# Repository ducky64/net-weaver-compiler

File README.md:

# net-weaver-compiler
Backend compiler for NetWeaver / WebEDG

See the live site at [https://leomcelroy.com/net-weaver/](https://leomcelroy.com/net-weaver/).

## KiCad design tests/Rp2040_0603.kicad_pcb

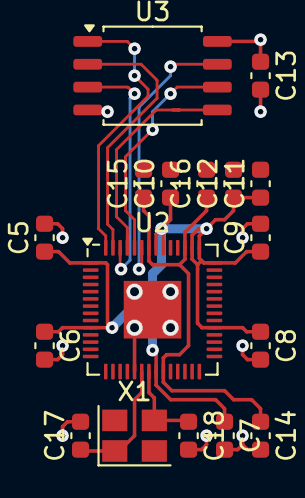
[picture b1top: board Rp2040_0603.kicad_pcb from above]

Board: 2 copper layers, 17 parts (0 on the bottom side), 11 nets.

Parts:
C5: Rp2040.iovdd_cap[0]; C_0603_1608Metric
C6: Rp2040.iovdd_cap[1]; C_0603_1608Metric
C7: Rp2040.iovdd_cap[2]; C_0603_1608Metric
C8: Rp2040.iovdd_cap[3]; C_0603_1608Metric
C9: Rp2040.iovdd_cap[4]; C_0603_1608Metric
C10: Rp2040.iovdd_cap[5]; C_0603_1608Metric
C11: Rp2040.avdd_cap; C_0603_1608Metric
C12: Rp2040.vreg_in_cap; C_0603_1608Metric
C13: Rp2040.mem.vcc_cap; C_0603_1608Metric
C14: Rp2040.dvdd_cap[0]; C_0603_1608Metric
C15: Rp2040.dvdd_cap[1]; C_0603_1608Metric
C16: Rp2040.vreg_out_cap; C_0603_1608Metric
C17: Rp2040.crystal.cap_a; C_0603_1608Metric
C18: Rp2040.crystal.cap_b; C_0603_1608Metric
U2: Rp2040.ic; QFN-56-1EP_7x7mm_P0.4mm_EP3.2x3.2mm
U3: Rp2040.mem.ic; SOIC-8_5.23x5.23mm_P1.27mm
X1: Rp2040.crystal.package; Crystal_SMD_3225-4Pin_3.2x2.5mm

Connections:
Hdc1080.pwr: C5.1, C6.1, C7.1, C8.1, C9.1, C10.1, C11.1, C12.1, C13.1, U2.1, U2.10, U2.22, U2.33, U2.42, U2.43, U2.44, U2.48, U2.49, U3.8
Rp2040.ic.qspi.miso: U2.55, U3.2
Rp2040.ic.qspi.mosi: U2.53, U3.5
Rp2040.ic.qspi.sck: U2.52, U3.6
Rp2040.ic.qspi_cs: U2.56, U3.1
Rp2040.ic.qspi_sd2: U2.54, U3.3
Rp2040.ic.qspi_sd3: U2.51, U3.7
Rp2040.ic.vreg_vout: C14.1, C15.1, C16.1, U2.23, U2.45, U2.50
Rp2040.xtal_node.xi: C17.1, U2.20, X1.1
Rp2040.xtal_node.xo: C18.1, U2.21, X1.3
UsbCReceptacle.gnd: C5.2, C6.2, C7.2, C8.2, C9.2, C10.2, C11.2, C12.2, C13.2, C14.2, C15.2, C16.2, C17.2, C18.2, U2.19, U2.57, U3.4, X1.2, X1.4

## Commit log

2024-02-23 wip add library to json dumper
2024-02-23 wip not really working =(
2024-02-23 wip pydantic
2024-02-23 pydantic working parsing
2024-02-23 pydantic working
2024-02-23 cleaning
2024-02-25 to HDL wip
2024-02-25 ugh paths
2024-02-25 compiling to netlist from netlist!
2024-02-25 better types
2024-02-25 wip slightly smarter array request detect
2024-02-27 update for new format
2024-03-02 wip unittest beginnings
2024-03-03 end to end unit test
2024-03-03 ports
2024-03-03 Update PolymorphicBlocks
2024-03-03 Update Dockerfile
2024-03-03 unit test working
2024-03-07 cleaning?
2024-03-14 no forms
2024-03-14 kill cors with fire
2024-03-14 kill it with fire 2
2024-03-15 add version endpoint
2024-03-15 ugh lol
2024-03-29 proper cors
2024-03-29 proper request directionality detection
2024-03-29 kinda working
2024-03-29 woking
2024-04-09 plumb through
2024-04-10 generate links
2024-04-10 structure definitions new
2024-04-10 wip kinda working something
2024-04-10 structured netlist data
2024-04-10 appears kinda working
2024-04-10 generate example footprints
2024-04-10 simpleBoardTop
2024-04-10 wip footprints
2024-04-10 footprint generator
2024-04-10 propagate footprints
2024-04-10 fix lib paths
2024-04-17 update, works
2024-04-20 hint signal direction, array direction, required
2024-04-22 compiler errors structured
2024-04-22 unit test for structured errors
2024-04-23 more validation + useful errors
2024-04-24 generate port and param docs
2024-04-26 new test cases
2024-04-26 autoreformat
2024-04-27 support new style arrays
2024-04-28 i2c device with multiple connection to array allocate test case
2024-04-30 update all the things
2024-04-30 fixes
2024-05-01 ship expected hdl
2024-05-02 cleanup for hdl updates
2024-05-22 update hdl to use submodules properly
2024-08-13 make library.json visible
2024-08-13 updated hdl incl ground refactor
2024-08-13 fix unittests
2024-08-27 generate PassiveConnectors
2024-08-27 sorted
2024-08-27 passiveconnector are array sinks
2024-09-03 ConnectorLed skeleton
2024-09-03 break up big app
2024-09-03 improved structure
2024-09-03 restructuring
2024-09-04 wip now a scoping bug
2024-09-05 connector gen working
2024-10-15 all the py files
2024-10-28 bump ver
2025-02-22 Update HDL submodule, update test expected footprint
2025-02-22 implicit i2c red test case
2025-02-23 Implicit I2C pullup generation w/ test case
2025-02-23 bump library
2025-02-23 suppress nuisance warnings
2025-03-17 Update to latest library
2025-06-20 precompute bbox data
2025-06-21 Disperse footprints (#7)
    Update HDL repo with WIP code that disperses footprints.
    A future PR may implement a hierarchical rectangular packing algorithm.
2025-06-22 Update latest libraries
2025-06-22 Add charlieplexing w/ RGB test case
2025-06-22 Add BoM generation
2025-06-22 Update examples
2025-06-22 I2C basic implicit device test
2025-06-23 generate full svgpcb board code
2025-06-23 Update HDL submodule
2025-06-25 Update HDL submodule (and its svgpcb codegen)
    Also removes the no-longer-used netlist output
2025-06-26 Support recursive parameters
2025-06-27 Update netlist config
